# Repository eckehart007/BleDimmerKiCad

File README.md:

Bluetooth 230AC dimmer switch with nRF51822 chip and with touch wheel as encoder and button..

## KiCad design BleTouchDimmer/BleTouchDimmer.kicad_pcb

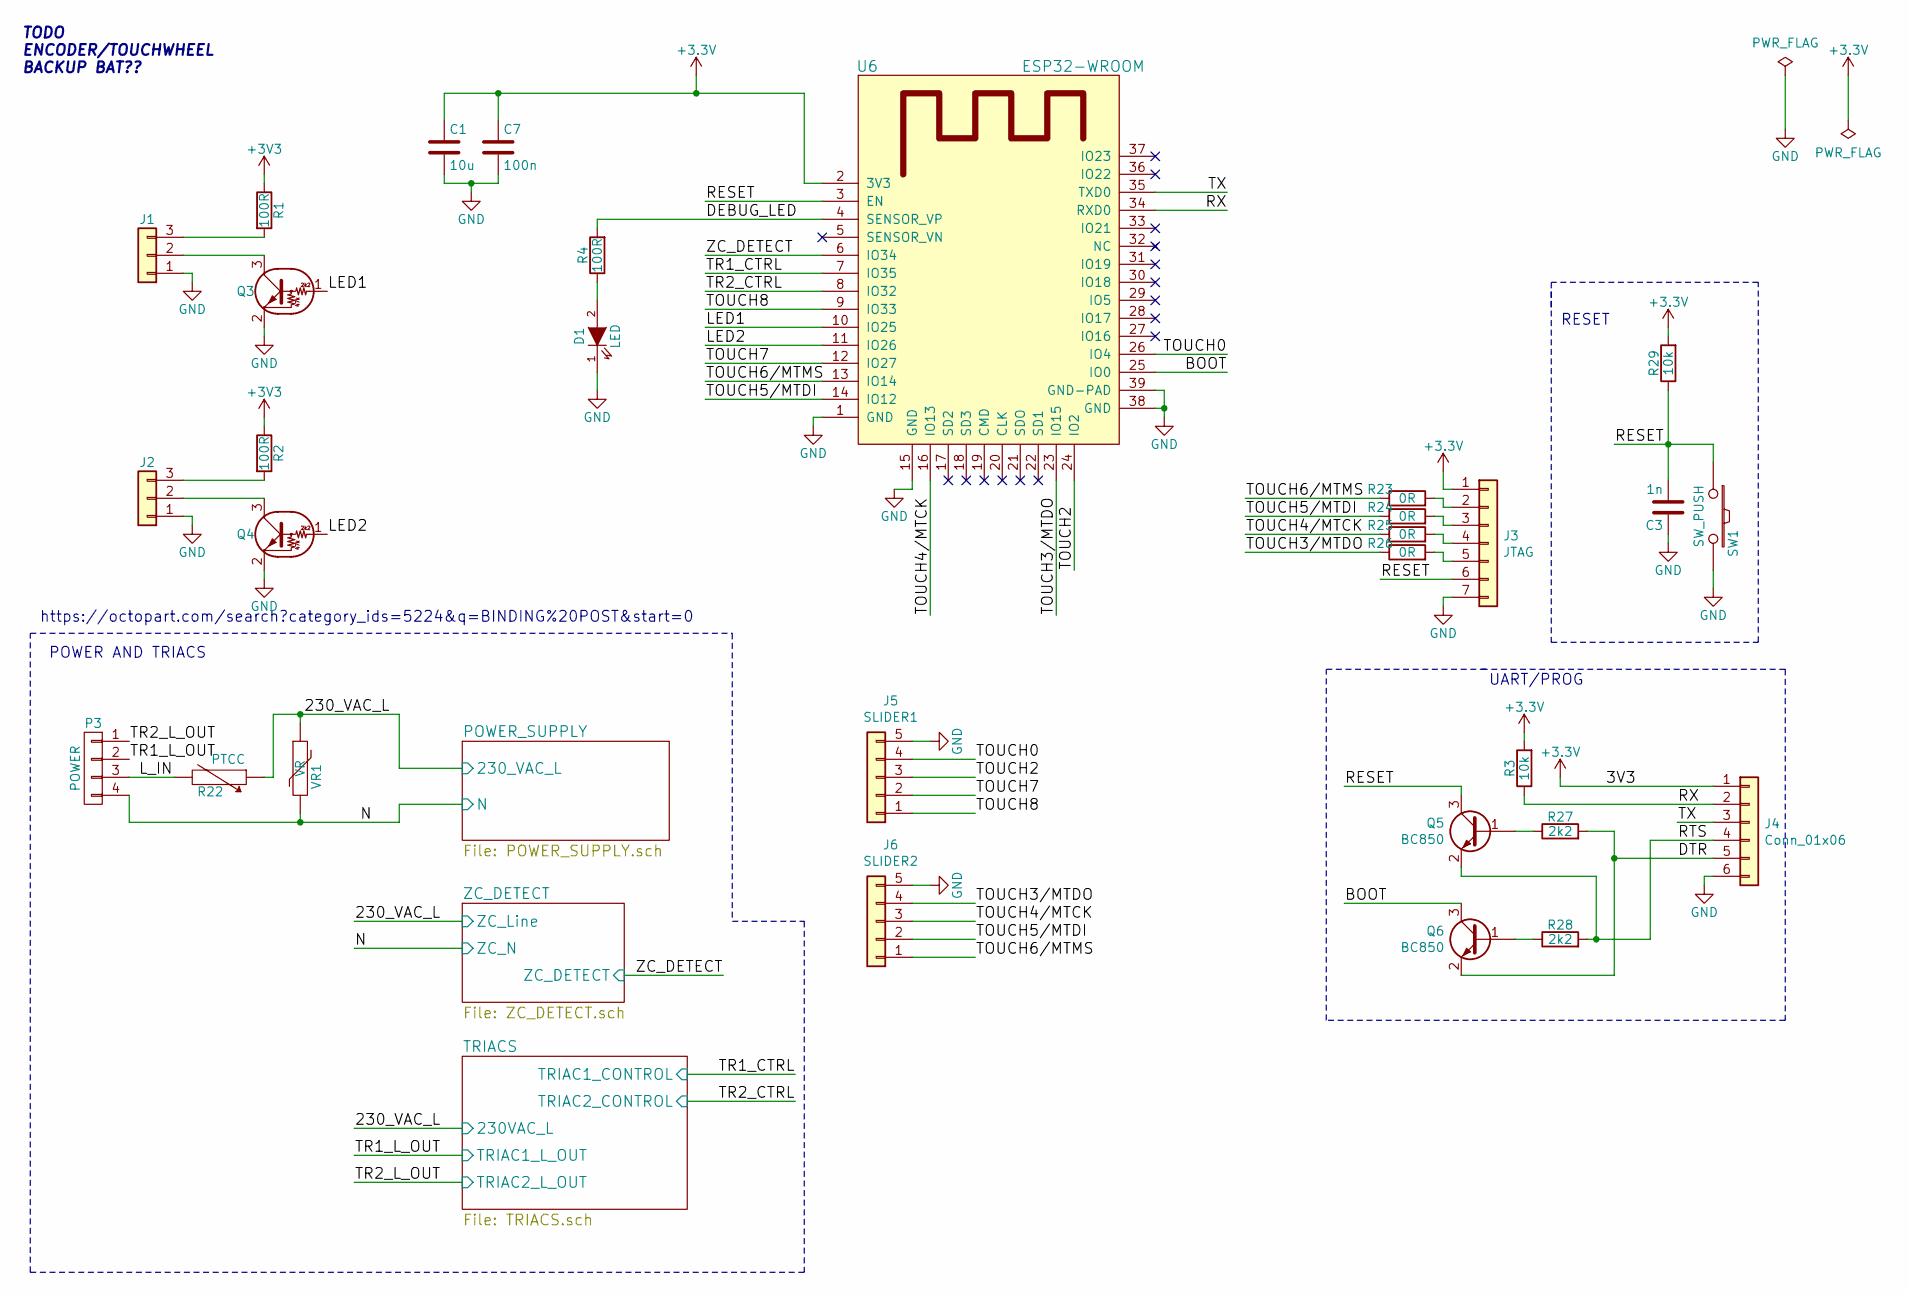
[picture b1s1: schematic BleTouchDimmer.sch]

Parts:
C1: 10u; C_0603
C3: 1n; C_0603
C7: 100n; C_0603
D1: LED; LED_0603
J1, J2: Conn_01x03; Molex_SPOX-5267_22-03-5035_03x2.54mm_Straight
J3: JTAG; Molex_SPOX-5267_22-03-5075_07x2.54mm_Straight
J4: Conn_01x06; Molex_SPOX-5267_22-03-5065_06x2.54mm_Straight
J5: SLIDER1; Molex_SPOX-5267_22-03-5055_05x2.54mm_Straight
J6: SLIDER2; Molex_SPOX-5267_22-03-5055_05x2.54mm_Straight
P3: POWER; TerminalBlock_Pheonix_MKDS1.5-4pol
Q3, Q4: PDTC123J; SOT-23
Q5, Q6: BC850; SOT-23
R1, R2, R4: 100R; R_0603
R3, R29: 10k; R_0603
R22: PTCC; RV_Disc_D7_W5.5_P5
R23, R24, R25, R26: 0R; R_0603
R27, R28: 2k2; R_0603
SW1: SW_PUSH; SW_SPST_B3SL-1022P
U6: ESP32-WROOM
VR1: VR; RV_Disc_D9_W4.4_P5

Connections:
/230_VAC_L: R22.1, VR1.1; also elsewhere on the board
/BOOT: Q6.3 (C), U6.25 (IO0)
/DEBUG_LED: R4.2, U6.4 (SENSOR_VP)
/DTR: J4.5, Q6.2 (E), R27.2
/LED1: Q3.1 (B), U6.10 (IO25)
/LED2: Q4.1 (B), U6.11 (IO26)
/L_IN: P3.3, R22.2
/N: P3.4, VR1.2; also elsewhere on the board
/RESET: C3.2, J3.6, Q5.3 (C), R29.1, SW1.1, U6.3 (EN)
/RTS: J4.4, Q5.2 (E), R28.2
/RX: J4.2, R3.1, U6.34 (RXD0)
/TOUCH0: J5.4, U6.26 (IO4)
/TOUCH2: J5.3, U6.24 (IO2)
/TOUCH3/MTDO: J6.4, R26.1, U6.23 (IO15)
/TOUCH4/MTCK: J6.3, R25.1, U6.16 (IO13)
/TOUCH5/MTDI: J6.2, R24.1, U6.14 (IO12)
/TOUCH6/MTMS: J6.1, R23.1, U6.13 (IO14)
/TOUCH7: J5.2, U6.12 (IO27)
/TOUCH8: J5.1, U6.9 (IO33)
/TR1_CTRL: U6.7 (IO35); also elsewhere on the board
/TR1_L_OUT: P3.2; also elsewhere on the board
/TR2_CTRL: U6.8 (IO32); also elsewhere on the board
/TR2_L_OUT: P3.1; also elsewhere on the board
/TX: J4.3, U6.35 (TXD0)
/ZC_DETECT: U6.6 (IO34); also elsewhere on the board
GND: C1.2, C3.1, C7.2, D1.1 (K), J1.1, J2.1, J3.7, J4.6, J5.5, J6.5, Q3.2 (E), Q4.2 (E), SW1.2, U6.1 (GND), U6.15 (GND), U6.38 (GND), U6.39 (GND-PAD); also elsewhere on the board
unnamed: D1.2 (A), R4.1
unnamed: J1.2, Q3.3 (C)
unnamed: J1.3, R1.2
unnamed: J2.2, Q4.3 (C)
unnamed: J2.3, R2.2
unnamed: J3.2, R23.2
unnamed: J3.3, R24.2
unnamed: J3.4, R25.2
unnamed: J3.5, R26.2
unnamed: Q5.1 (B), R27.1
unnamed: Q6.1 (B), R28.1

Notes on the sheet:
UART/PROG
POWER AND TRIACS
TODO ENCODER/TOUCHWHEEL BACKUP BAT??
RESET
https://octopart.com/search?category_ids=5224&q=BINDING%20POST&start=0

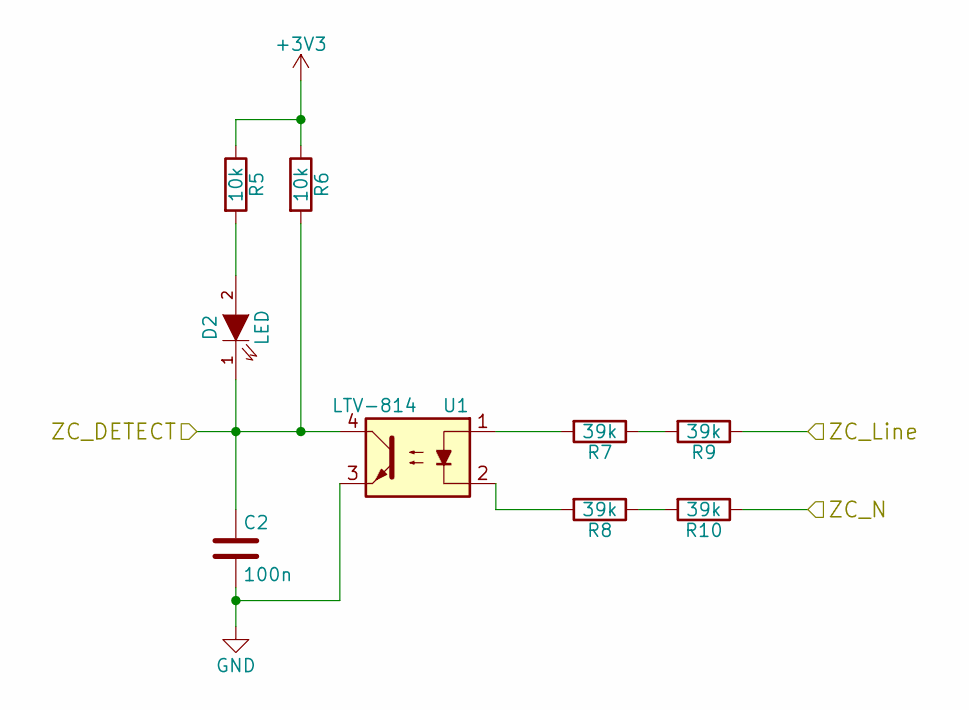
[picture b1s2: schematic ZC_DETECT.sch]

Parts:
C2: 100n; C_0603
D2: LED; LED_0603
R5, R6: 10k; R_0603
R7, R8, R9, R10: 39k; R_1210
U1: LTV-814; Optocoupler_SMD_LTV-817S

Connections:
/230_VAC_L: R9.1; also elsewhere on the board
/N: R10.1; also elsewhere on the board
/ZC_DETECT: C2.1, D2.1 (K), R6.2, U1.4; also elsewhere on the board
GND: C2.2, U1.3; also elsewhere on the board
unnamed: D2.2 (A), R5.2
unnamed: R7.1, R9.2
unnamed: R7.2, U1.1
unnamed: R8.2, U1.2
unnamed: R8.1, R10.2

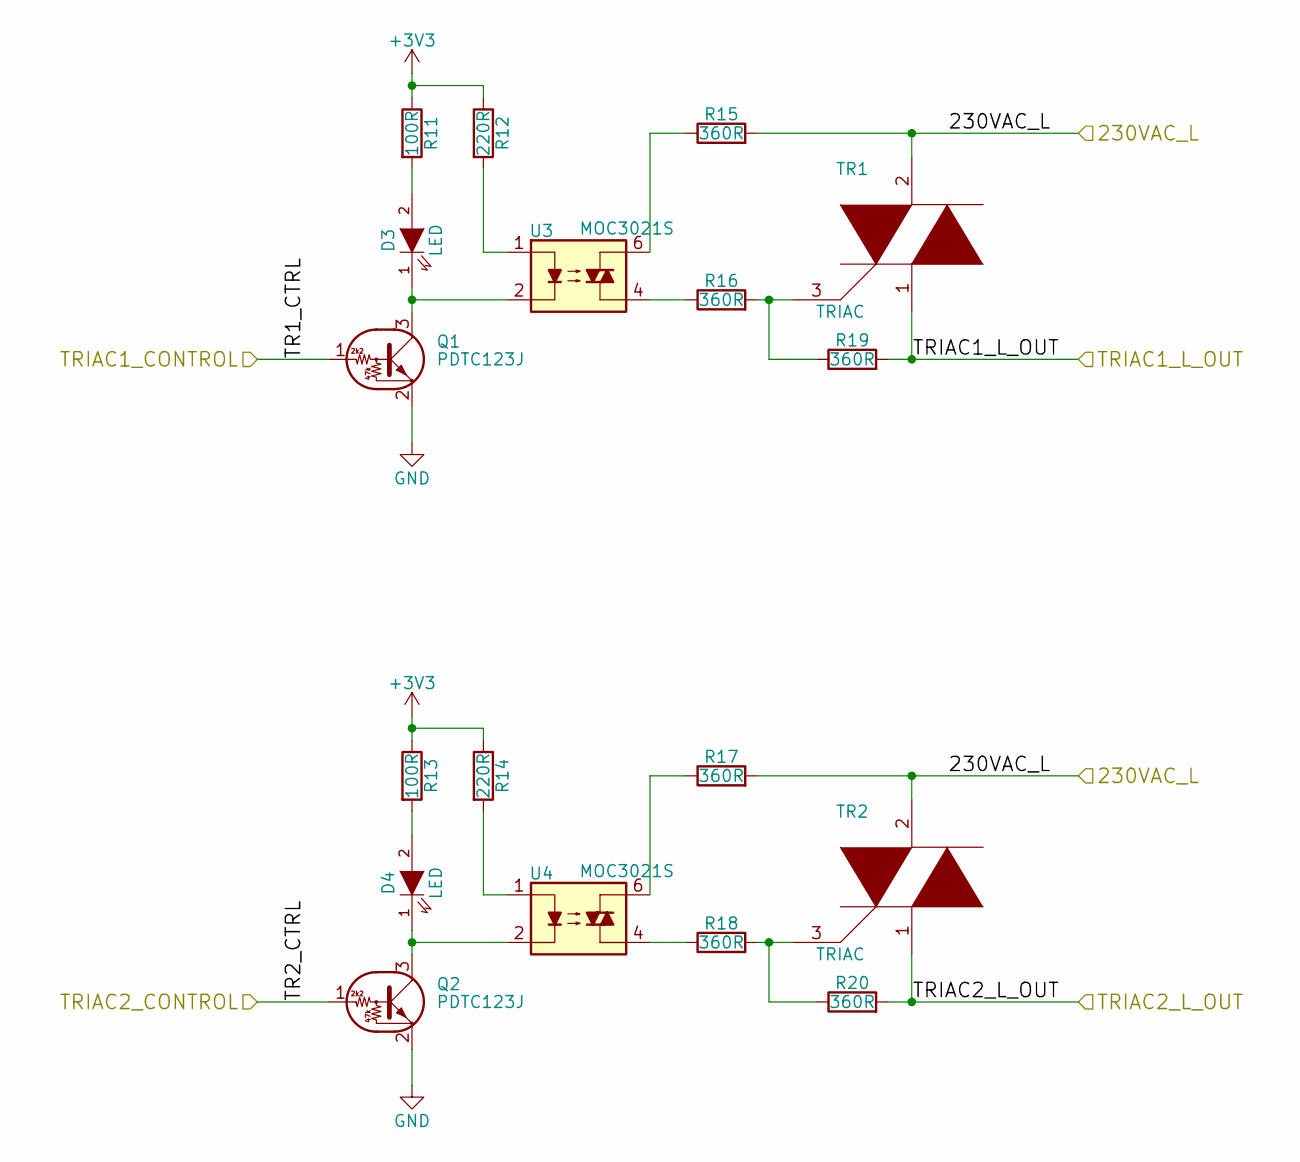
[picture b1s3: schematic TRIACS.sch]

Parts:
D3, D4: LED; LED_0603
Q1, Q2: PDTC123J; SOT-23
R11, R13: 100R; R_0603
R12, R14: 220R; R_0603
R15, R16, R17, R18, R19, R20: 360R; R_1206
TR1, TR2: TRIAC; TO-252-2Lead
U3, U4: MOC3021S

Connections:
/230_VAC_L: R15.2, R17.2, TR1.2, TR2.2; also elsewhere on the board
/TR1_CTRL: Q1.1 (B); also elsewhere on the board
/TR1_L_OUT: R19.2, TR1.1; also elsewhere on the board
/TR2_CTRL: Q2.1 (B); also elsewhere on the board
/TR2_L_OUT: R20.2, TR2.1; also elsewhere on the board
GND: Q1.2 (E), Q2.2 (E); also elsewhere on the board
unnamed: D3.1 (K), Q1.3 (C), U3.2
unnamed: D3.2 (A), R11.2
unnamed: D4.1 (K), Q2.3 (C), U4.2
unnamed: D4.2 (A), R13.2
unnamed: R12.2, U3.1
unnamed: R14.2, U4.1
unnamed: R15.1, U3.6
unnamed: R16.1, U3.4
unnamed: R16.2, R19.1, TR1.3
unnamed: R17.1, U4.6
unnamed: R18.1, U4.4
unnamed: R18.2, R20.1, TR2.3

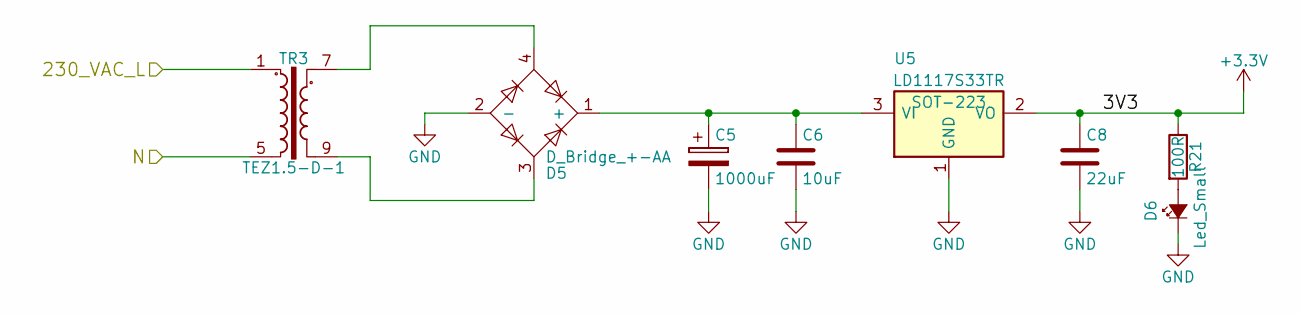
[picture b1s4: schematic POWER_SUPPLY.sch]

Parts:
C5: 1000uF; CP_Radial_D10.0mm_P5.00mm
C6: 10uF; C_0603
C8: 22uF; C_0603
D5: D_Bridge_+-AA; SOIC-4
D6: Led_Small; LED_0603
R21: 100R; R_0603
TR3: TEZ1.5-D-1; TEZ-28x33
U5: LD1117S33TR; SOT-223

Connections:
/230_VAC_L: TR3.1; also elsewhere on the board
/N: TR3.5; also elsewhere on the board
GND: C5.2, C6.2, C8.2, D5.2 (-), D6.1 (K), U5.1 (GND); also elsewhere on the board
unnamed: C5.1, C6.1, D5.1 (+), U5.3 (VI)
unnamed: D5.3, TR3.9
unnamed: D5.4, TR3.7
unnamed: D6.2 (A), R21.2

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
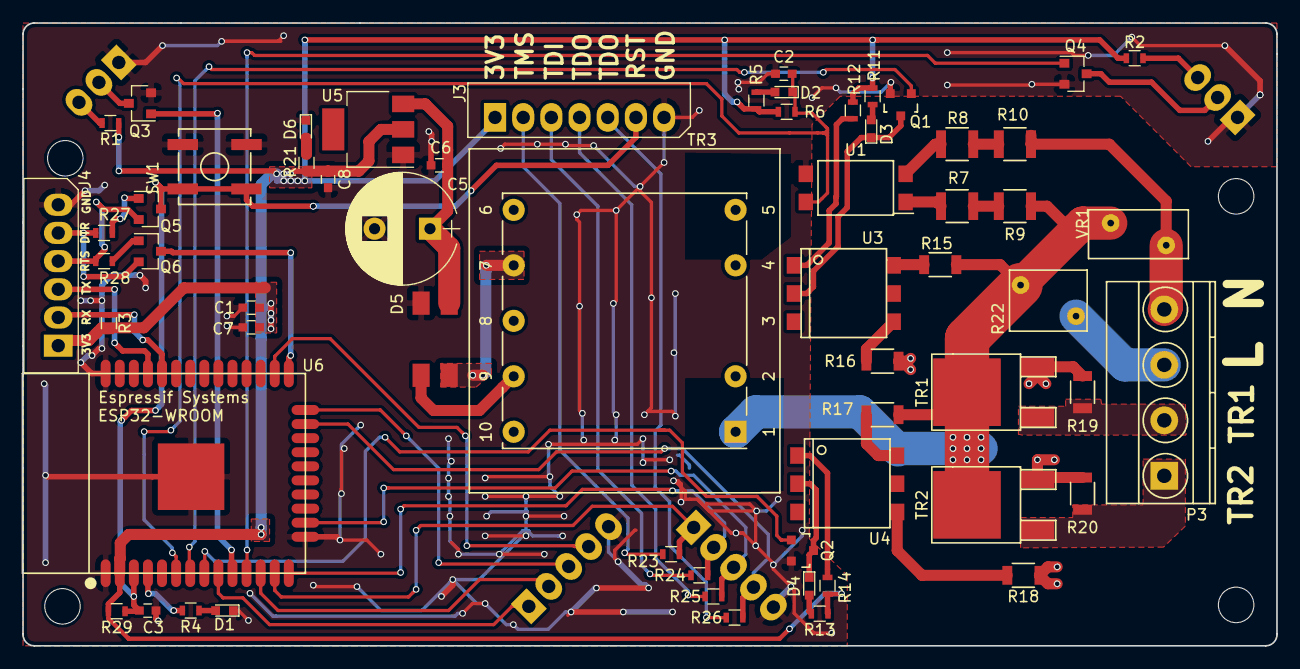
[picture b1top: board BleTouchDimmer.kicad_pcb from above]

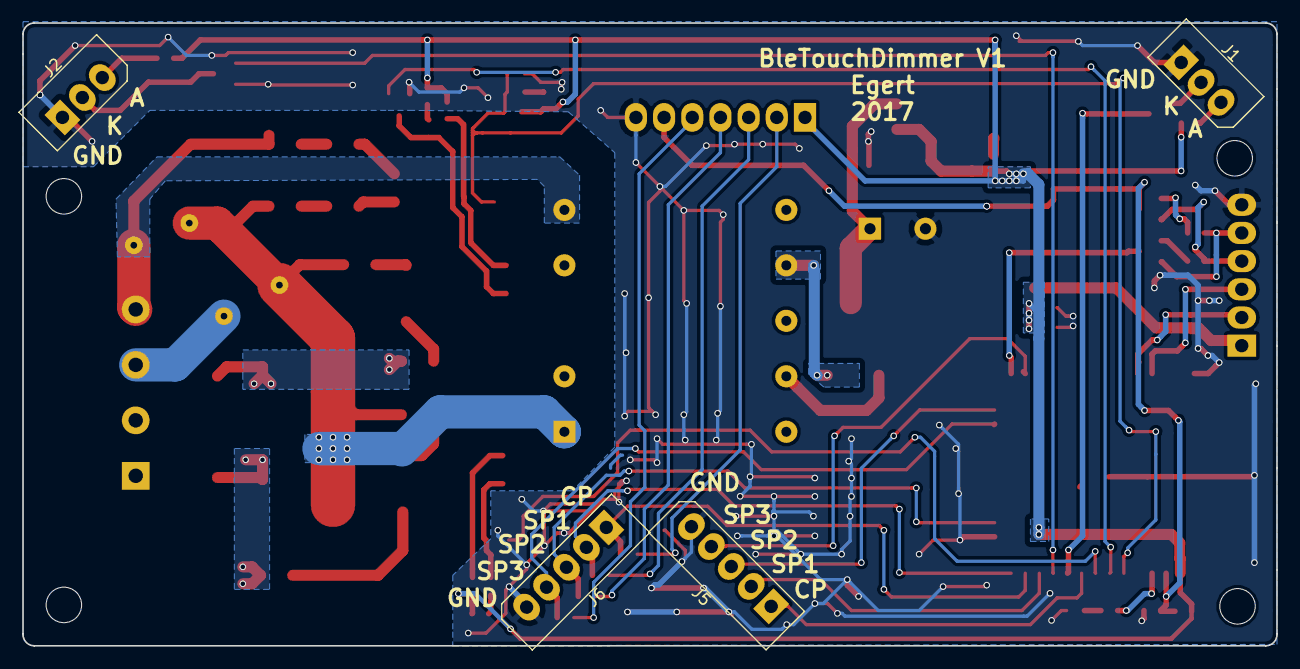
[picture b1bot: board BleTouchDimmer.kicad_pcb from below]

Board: 2 copper layers, 113.0 x 56.1 mm, 65 parts (4 on the bottom side), 59 nets.

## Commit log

2016-07-24 Created KiCad schematic.
2016-07-24 Changed library settings.
2016-07-24 Added nRF51 and crystal.
2016-07-25 Started rf part.
2016-11-01 Added component MDBT40.
2016-11-02 Removed nRF51 symbol.
2016-11-05 Added uart, reset and programming part.
2016-11-05 Updated RESET part.
2016-11-06 Started ZC_detect part. TODO select optoisolator.
2016-11-06 Updated ZC part.
2016-11-07 Started Triac logic.
2016-11-09 Changed MOC3021S footprint.
2016-11-09 Added triacs.
2016-11-09 Added terminal block.
2016-11-10 Added comments about possible power supply solutions.
2016-11-10 Added power supply link LNK4002S.
2016-11-11 ADDED LNK4002S
2016-11-12 Selected diode bridge.
2016-11-12 Small changes.
2016-11-16 Added isolation transformer:D
2016-11-18 Updated power supply with LDO LD1117. TODO - Protection (VARISTOR, ??)
2016-11-18 Added varistor (Small??)
2016-11-18 Finished power supply and protection circuit, connected all sheets.
2016-11-18 Started cap sensor logic.
2016-11-23 Added lib
2017-10-15 Uncommited changes.
2017-10-27 Started changing controller to esp32-wroom module.
2017-10-28 Updated schematic.
2017-10-29 Started placing footprints on pcb. Maybe needs to split pcb to power part and controller part.
2017-10-29 Added comment about cheaper terminal block solution.
2017-10-29 Started larger pcb with 2 slider wheel PCBs.
2017-10-30 Verified slider pcb position.
2017-11-03 Started routing triacs.
2017-11-04 Finished routing. Needs to be verified.
2017-11-04 Spreaded pcb wires to get less crosstalk.
2017-11-04 Made small changes and generated gerbers.
2017-11-04 New gerbers and ordered pcbs.
2017-12-27 uncommited changes??
